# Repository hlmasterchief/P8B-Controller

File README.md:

# P8B-Controller
Repository for files for an open source gamepad using the Noridc NRF51822 microcontroller.

## Intro
This repository contains all files used to create a BLE gamepad using the Nordic NRF51822 microcontroller. I am using the MDBT40-P module that is approved by Nordic for this project instead of using the NRF51822 directly. 

## File Structure
The schematic and bill of materials can be found at the root layer and Gerber files for the layout can be found in the Gerber directory. The actual project files are found in the Controller directory and the project itself was created with a nightly build of [KiCad](http://kicad-pcb.org/). I used a nightly build because it addresses many issues I was having with the "stable" version of KiCad. For reference I am currently using revision 6687.

## License
This project is released under the Creative Commons Attribution and Share-alike license. The details can be found in LICENSE.txt but in summary, you can use the contents of this project however you want, including commercial use, if you:
1. Release your derivative projects/products with the same license as this one and
2. Attribute me in all derivative works.

###Author Info
[Nate Thompson](mailto:nate@prime8bit.com) <br/>
[http://prime8bit.com](http://prime8bit.com)

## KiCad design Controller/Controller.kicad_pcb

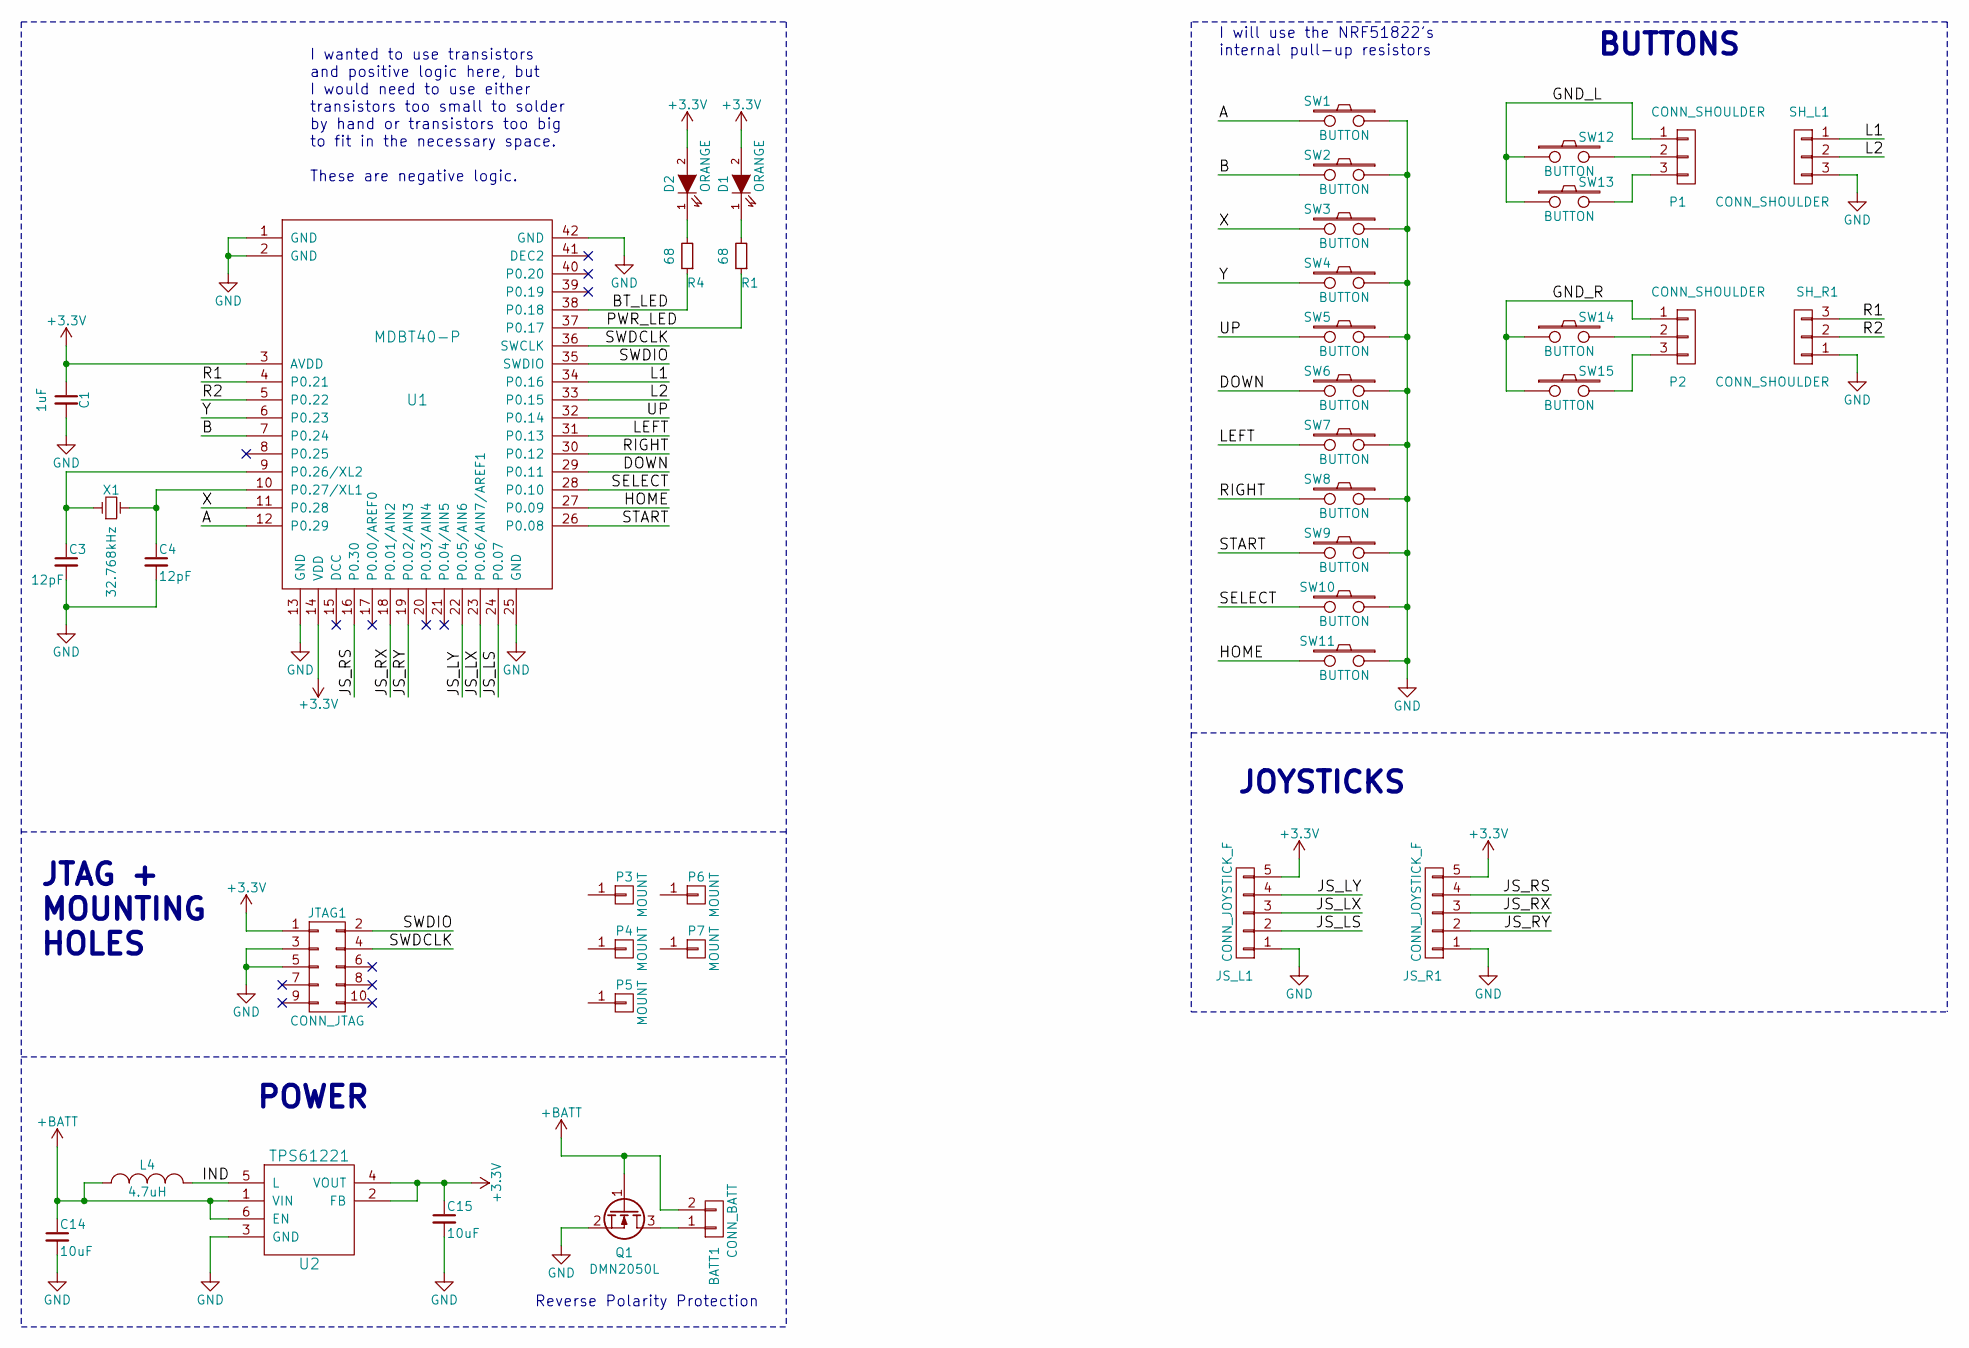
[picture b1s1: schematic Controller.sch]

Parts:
BATT1: CONN_BATT; Manufacturer Part Number S5B-ZR(LF)(SN)
C1: 1uF; C_0805; Manufacturer Part Number CL21F105ZOCNNNC
C3, C4: 12pF; C_0805; Manufacturer Part Number CL21C120FBANNNC
C14, C15: 10uF; C_0805; Manufacturer Part Number CL21A106KQFNNNE
D1, D2: ORANGE; LED_0805; Manufacturer Part Number LTST-C170KFKT
JS_L1: CONN_JOYSTICK_F; CONN_JOYSTICK; Manufacturer Part Number S5B-ZR(LF)(SN)
JS_R1: CONN_JOYSTICK_F; CONN_JOYSTICK; Manufacturer Part Number S5B-ZR(LF)(SN)
JTAG1: CONN_JTAG; Pin_Header_Straight_2x05_Pitch1.27mm; Manufacturer Part Number 20021111-00010T4LF
L4: 4.7uH; NR3015T4R7M; Manufacturer Part Number NR3015T4R7M
P1, P2: CONN_SHOULDER; CONN_SHOULDER_M; Manufacturer Part Number B3B-ZR(LF)(SN)
P3, P4, P5, P6, P7: MOUNT; Mounting_#2
Q1: DMN2050L; SOT-23-3; Manufacturer Part Number DMN2050L-7
R1, R4: 68; R_0805; Manufacturer Part Number ERJ-6ENF68R0V
SH_L1: CONN_SHOULDER; CONN_SHOULDER_F; Manufacturer Part Number B3B-ZR(LF)(SN)
SH_R1: CONN_SHOULDER; CONN_SHOULDER_F; Manufacturer Part Number B3B-ZR(LF)(SN)
SW1, SW2, SW3, SW4, SW5, SW6, SW7, SW8, SW9, SW10, SW11, SW12, SW13, SW14, SW15: BUTTON; SW_BUTTON; Manufacturer Part Number PTS525SM15SMTR2 LFS
U1: MDBT40-P; Manufacturer Part Number MDBT40P-P256V3
U2: TPS61221; Manufacturer Part Number TPS61221DCKT
X1: 32.768kHz; Manufacturer Part Number ST3215SB32768E0HPWBB

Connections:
+3V3: C1.1, C15.1, D1.2 (A), D2.2 (A), JS_L1.5, JS_R1.5, JTAG1.1, U1.3 (AVDD), U1.14 (VDD), U2.2 (FB), U2.4 (VOUT)
+BATT: BATT1.2, C14.1, L4.1, Q1.1 (G), U2.1 (VIN), U2.6 (EN)
/A: SW1.2, U1.12 (P0.29)
/B: SW2.2, U1.7 (P0.24)
/BT_LED: R4.1, U1.38 (P0.18)
/DOWN: SW6.2, U1.29 (P0.11)
/GND_L: P1.1, SW12.1, SW13.1
/GND_R: P2.1, SW14.1, SW15.1
/HOME: SW11.2, U1.27 (P0.09)
/IND: L4.2, U2.5 (L)
/JS_LS: JS_L1.2, U1.24 (P0.07)
/JS_LX: JS_L1.3, U1.23 (P0.06/AIN7/AREF1)
/JS_LY: JS_L1.4, U1.22 (P0.05/AIN6)
/JS_RS: JS_R1.4, U1.16 (P0.30)
/JS_RX: JS_R1.3, U1.18 (P0.01/AIN2)
/JS_RY: JS_R1.2, U1.19 (P0.02/AIN3)
/L1: SH_L1.1, U1.34 (P0.16)
/L2: SH_L1.2, U1.33 (P0.15)
/LEFT: SW7.2, U1.31 (P0.13)
/PWR_LED: R1.1, U1.37 (P0.17)
/R1: SH_R1.3, U1.4 (P0.21)
/R2: SH_R1.2, U1.5 (P0.22)
/RIGHT: SW8.2, U1.30 (P0.12)
/SELECT: SW10.2, U1.28 (P0.10)
/START: SW9.2, U1.26 (P0.08)
/SWDCLK: JTAG1.4, U1.36 (SWCLK)
/SWDIO: JTAG1.2, U1.35 (SWDIO)
/UP: SW5.2, U1.32 (P0.14)
/X: SW3.2, U1.11 (P0.28)
/Y: SW4.2, U1.6 (P0.23)
GND: C1.2, C3.2, C4.2, C14.2, C15.2, JS_L1.1, JS_R1.1, JTAG1.3, JTAG1.5, Q1.2 (S), SH_L1.3, SH_R1.1, SW1.1, SW2.1, SW3.1, SW4.1, SW5.1, SW6.1, SW7.1, SW8.1, SW9.1, SW10.1, SW11.1, U1.1 (GND), U1.2 (GND), U1.13 (GND), U1.25 (GND), U1.42 (GND), U2.3 (GND)
unnamed: BATT1.1, Q1.3 (D)
unnamed: C3.1, U1.9 (P0.26/XL2), X1.1
unnamed: C4.1, U1.10 (P0.27/XL1), X1.2
unnamed: D1.1 (K), R1.2
unnamed: D2.1 (K), R4.2
unnamed: P1.2, SW12.2
unnamed: P1.3, SW13.2
unnamed: P2.2, SW14.2
unnamed: P2.3, SW15.2

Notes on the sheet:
POWER
JTAG + MOUNTING HOLES
I wanted to use transistors and positive logic here, but I would need to use either transistors too small to solder by hand or transistors too big to fit in the necessary space. These are negative logic.
Reverse Polarity Protection
I will use the NRF51822's internal pull-up resistors
BUTTONS
JOYSTICKS

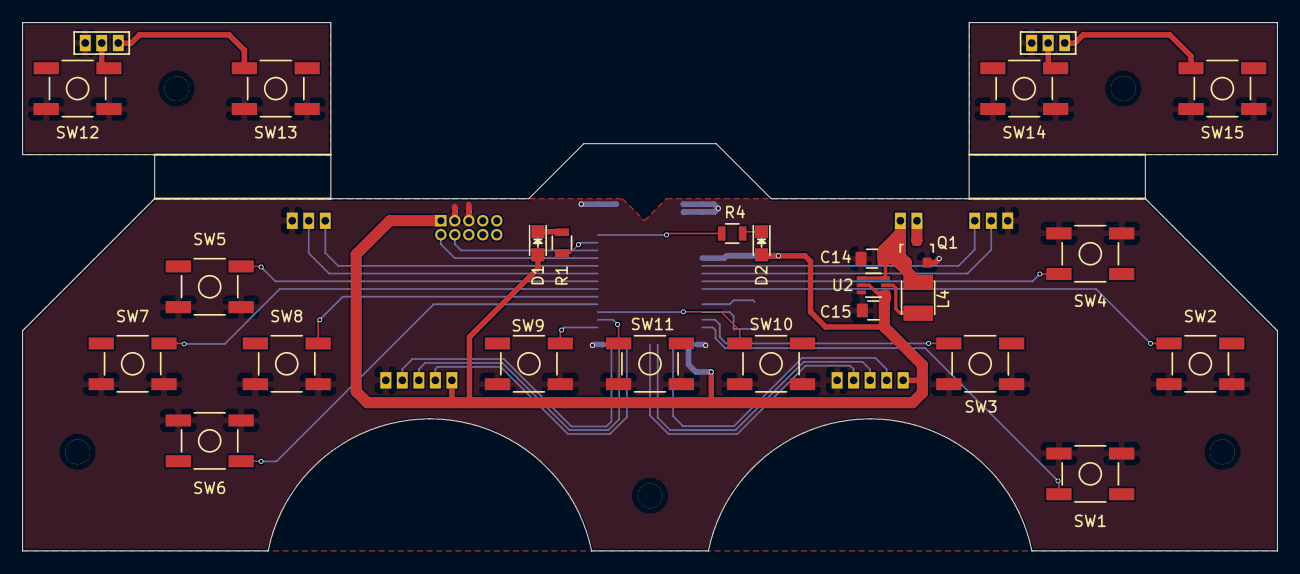
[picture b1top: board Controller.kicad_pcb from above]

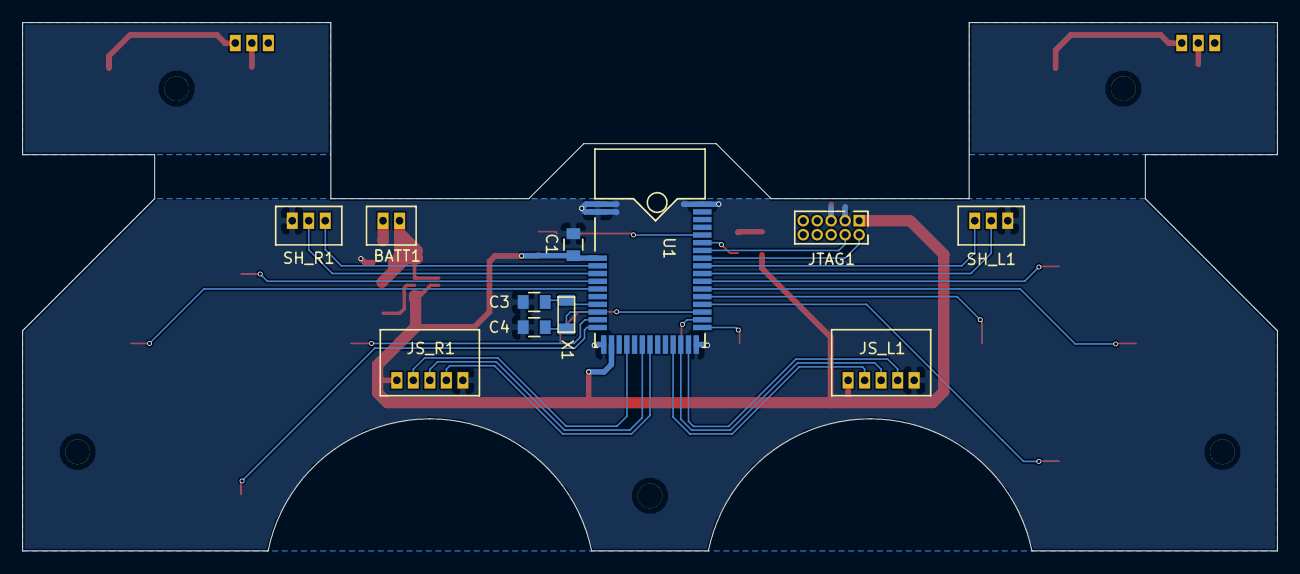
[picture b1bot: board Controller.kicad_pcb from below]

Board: 2 copper layers, 114.0 x 48.0 mm, 42 parts (11 on the bottom side), 40 nets.

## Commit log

2016-04-14 Initial Commit.
2016-04-14 Renamed Schematic for clarity.
2016-04-21 Improved traces in power supply circuit. Added clearance on inside of drill holes. Removed sharp inside corners and replaced with cirular cutouts. Removed removed pull-down resistors because I am usi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
2016-04-21 Improved routing for power supply circuit. Added clearance to inside of screw holes. Replaced sharp inner corners on bottom of the board with round holes. Removed pull-down resistors and opted for ne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
2016-04-21 Updated BOM.xlsx
